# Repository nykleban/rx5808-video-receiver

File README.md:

# Smart FPV Analog RX & Spectral Analyzer

**Проєкт:** апаратно-програмний комплекс для прийому аналогового FPV-відеосигналу 5.8 GHz та сканування радіочастотного спектра в реальному часі.

---

## Про Проєкт

Цей репозиторій містить вихідний код прошивки, десктопного додатку та файли проєкту друкованої плати для розумного FPV-приймача. Система побудована на базі мікроконтролера **ATmega328P**, високочастотного модуля **RX5808** та розширеної системи керування живленням для забезпечення стабільних аналогових вимірювань.

Проєкт поєднує низькорівневе програмування вбудованих систем, розробку 4-шарової PCB з високими вимогами до розведення RF, силових та аналогових вузлів, а також десктопний аналізатор на Python. Проєкт розроблено в рамках інженерно-практичної роботи програми робототехніки Інституту ІТ та бізнесу.

Плата спроєктована в KiCad і замовлена через JLCPCB. На момент підготовки репозиторію плата ще не доставлена, тому в репозиторії подані проєктні матеріали: схема, PCB-layout, production-файли, 3D-рендери та скріншоти програмної частини.

---

## Основні Характеристики системи

### Hardware

- **RF-модуль:** приймач **RX5808 5.8 GHz** із керуванням через SPI для вибору частоти.
- **Мікроконтролер:** **ATmega328P** із зовнішнім кварцовим резонатором 16 MHz.
- **Power Management:** контролер заряду **Texas Instruments BQ25703A**, апаратний захист акумулятора **HY2120-CB**, шунти для вимірювання струму.
- **Інтерфейси:** **USB Type-C**, **CP2102N USB-to-UART**, торцевий **SMA edge-mount** роз'єм для FPV-антени.

### Software

- **Firmware C/C++:** прошивка для ATmega328P із керуванням RX5808 через SPI, зчитуванням RSSI через ADC, I2C-взаємодією з BQ25703A та serial logging.
- **Python GUI:** десктопний додаток для візуалізації RSSI в реальному часі та перевірки рівня сигналу на обраній частоті.

---

## Основні можливості

- прийом аналогового FPV-сигналу 5.8 GHz через RX5808;
- перемикання FPV-частот через SPI-керування RX5808;
- зчитування RSSI для оцінки рівня сигналу;
- виведення band, channel, frequency та RSSI через serial log;
- візуалізація RSSI в desktop analyzer у реальному часі;
- підготовлена 4-шарова PCB з окремими RF, MCU та power-management блоками;
- production package для виготовлення плати.

---

## Архітектура Друкованої Плати (PCB Layout)

Плата розроблена як 4-шарова PCB товщиною 1.6 мм з урахуванням суворих правил трасування:

1. **Ізоляція шумів:** силовий імпульсний блок з BQ25703A максимально віддалений від аналогової частини приймача RX5808.
2. **Розділення функціональних блоків:** RF, MCU, USB/UART та power-management частини винесені в окремі зони плати.
3. **Екранування:** GND-полігони використовуються для зменшення шумів і покращення стабільності аналогових вимірювань.
4. **Production-ready структура:** підготовлено BOM, positions, designators, IPC netlist і production archive для виготовлення плати.

---

## Firmware

Прошивка для ATmega328P реалізує:

- SPI-керування RX5808;
- вибір FPV-частоти;
- зчитування RSSI через ADC;
- I2C-взаємодію з power-management контролером;
- serial logging для перевірки каналу, частоти та RSSI.

Файл прошивки: `CODE/fpv_receiver.ino`

---

## Desktop analyzer

Python-додаток використовується для перегляду RSSI в реальному часі. Він дає змогу візуально порівнювати рівень сигналу на різних каналах і бачити стабільність прийому.

Використані технології: Python, PyQt5, pyqtgraph, pyserial, NumPy.

Файл додатку: `CODE/main.py`

---

## Структура репозиторію

```text
.
├── CODE/                         # firmware and desktop analyzer
│   ├── fpv_receiver.ino
│   └── main.py
├── IMAGES/                       # renders, schematics and analyzer screenshots
├── Custom_Libs/                  # custom KiCad symbols and footprints
├── production/                   # BOM, positions, designators, netlist
├── atmega328.kicad_pcb           # PCB layout
├── atmega328.kicad_sch           # main schematic
├── mcu_atmega_spi.kicad_sch      # MCU/SPI schematic block
├── rx5808_rf.kicad_sch           # RF schematic block
├── power_usb_battery_buck.kicad_sch
└── production.zip
```

---

## Візуальні матеріали

### PCB та схема

### RSSI analyzer

---

## Production files

Папка `production/` містить матеріали для виготовлення та перевірки плати:

- `bom.csv`;
- `positions.csv`;
- `designators.csv`;
- `netlist.ipc`;
- `atmega328.zip`.

Також у корені є `production.zip` як готовий архів production package.

---

## Поточний статус

- schematic design completed;
- 4-layer PCB layout completed;
- production files generated;
- PCB ordered through JLCPCB;
- firmware and desktop analyzer added to the repository;
- RSSI analyzer screenshots included.

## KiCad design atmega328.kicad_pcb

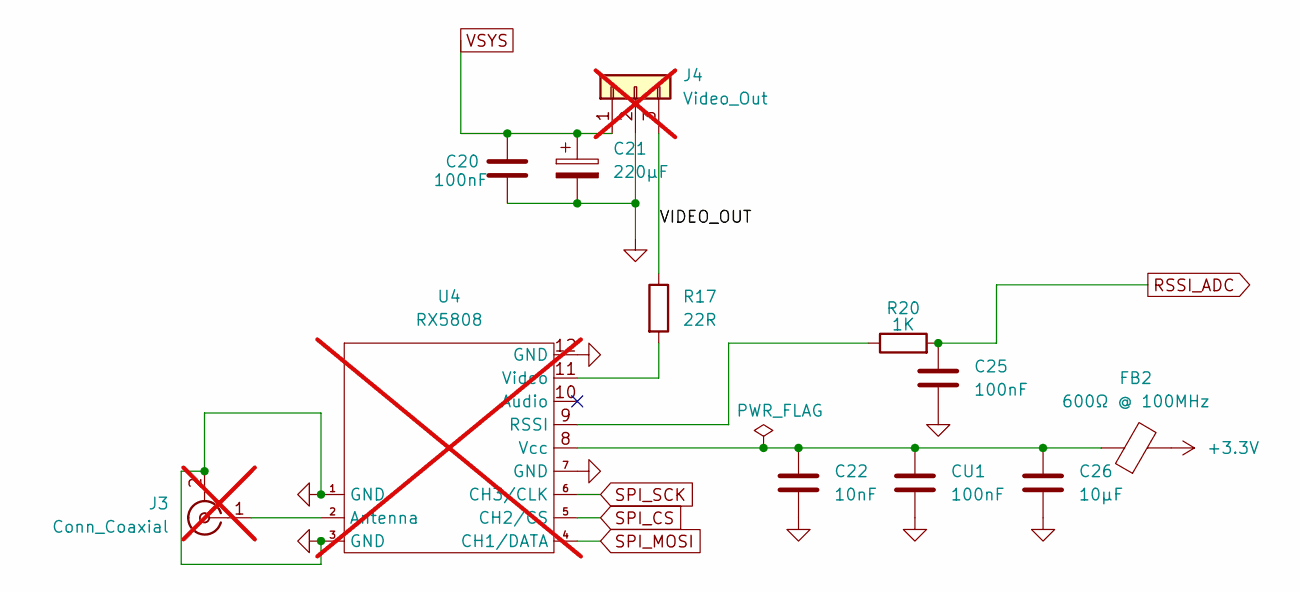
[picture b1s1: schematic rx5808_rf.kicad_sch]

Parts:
C20, C25: 100nF; C_0805_2012Metric; LCSC C1711
C21: 220µF; CP_Elec_8x10; LCSC C136294
C22: 10nF; C_0805_2012Metric; LCSC C1710
C26: 10µF; C_0805_2012Metric; LCSC C7469956
CU1: 100nF; C_0805_2012Metric; LCSC C1711
FB2: 600Ω @ 100MHz; R_0805_2012Metric; LCSC C21519
J3: Conn_Coaxial; SMA_Amphenol_132289_EdgeMount; LCSC C20415780; not fitted
J4: Video_Out; PinHeader_1x03_P2.54mm_Vertical; not fitted
R17: 22R; R_0805_2012Metric; LCSC C441970
R20: 1К; R_0805_2012Metric; LCSC C844939
U4: RX5808; not fitted

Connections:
+3.3V: FB2.2; also elsewhere on the board
/RX5808/VIDEO_OUT: J4.3, R17.1
GND: C20.2, C21.2, C22.2, C25.2, C26.2, CU1.2, J3.2 (Ext), J4.2, U4.1 (GND), U4.3 (GND), U4.7 (GND), U4.12 (GND); also elsewhere on the board
unnamed: J3.1 (In), U4.2 (Antenna)
unnamed: R20.1, U4.9 (RSSI)
unnamed: C22.1, C26.1, CU1.1, FB2.1, U4.8 (Vcc)
unnamed: R17.2, U4.11 (Video)
RSSI_ADC: C25.1, R20.2; also elsewhere on the board
SPI_CS: U4.5 (CH2/CS); also elsewhere on the board
SPI_MOSI: U4.4 (CH1/DATA); also elsewhere on the board
SPI_SCK: U4.6 (CH3/CLK); also elsewhere on the board
VSYS: C20.1, C21.1, J4.1; also elsewhere on the board

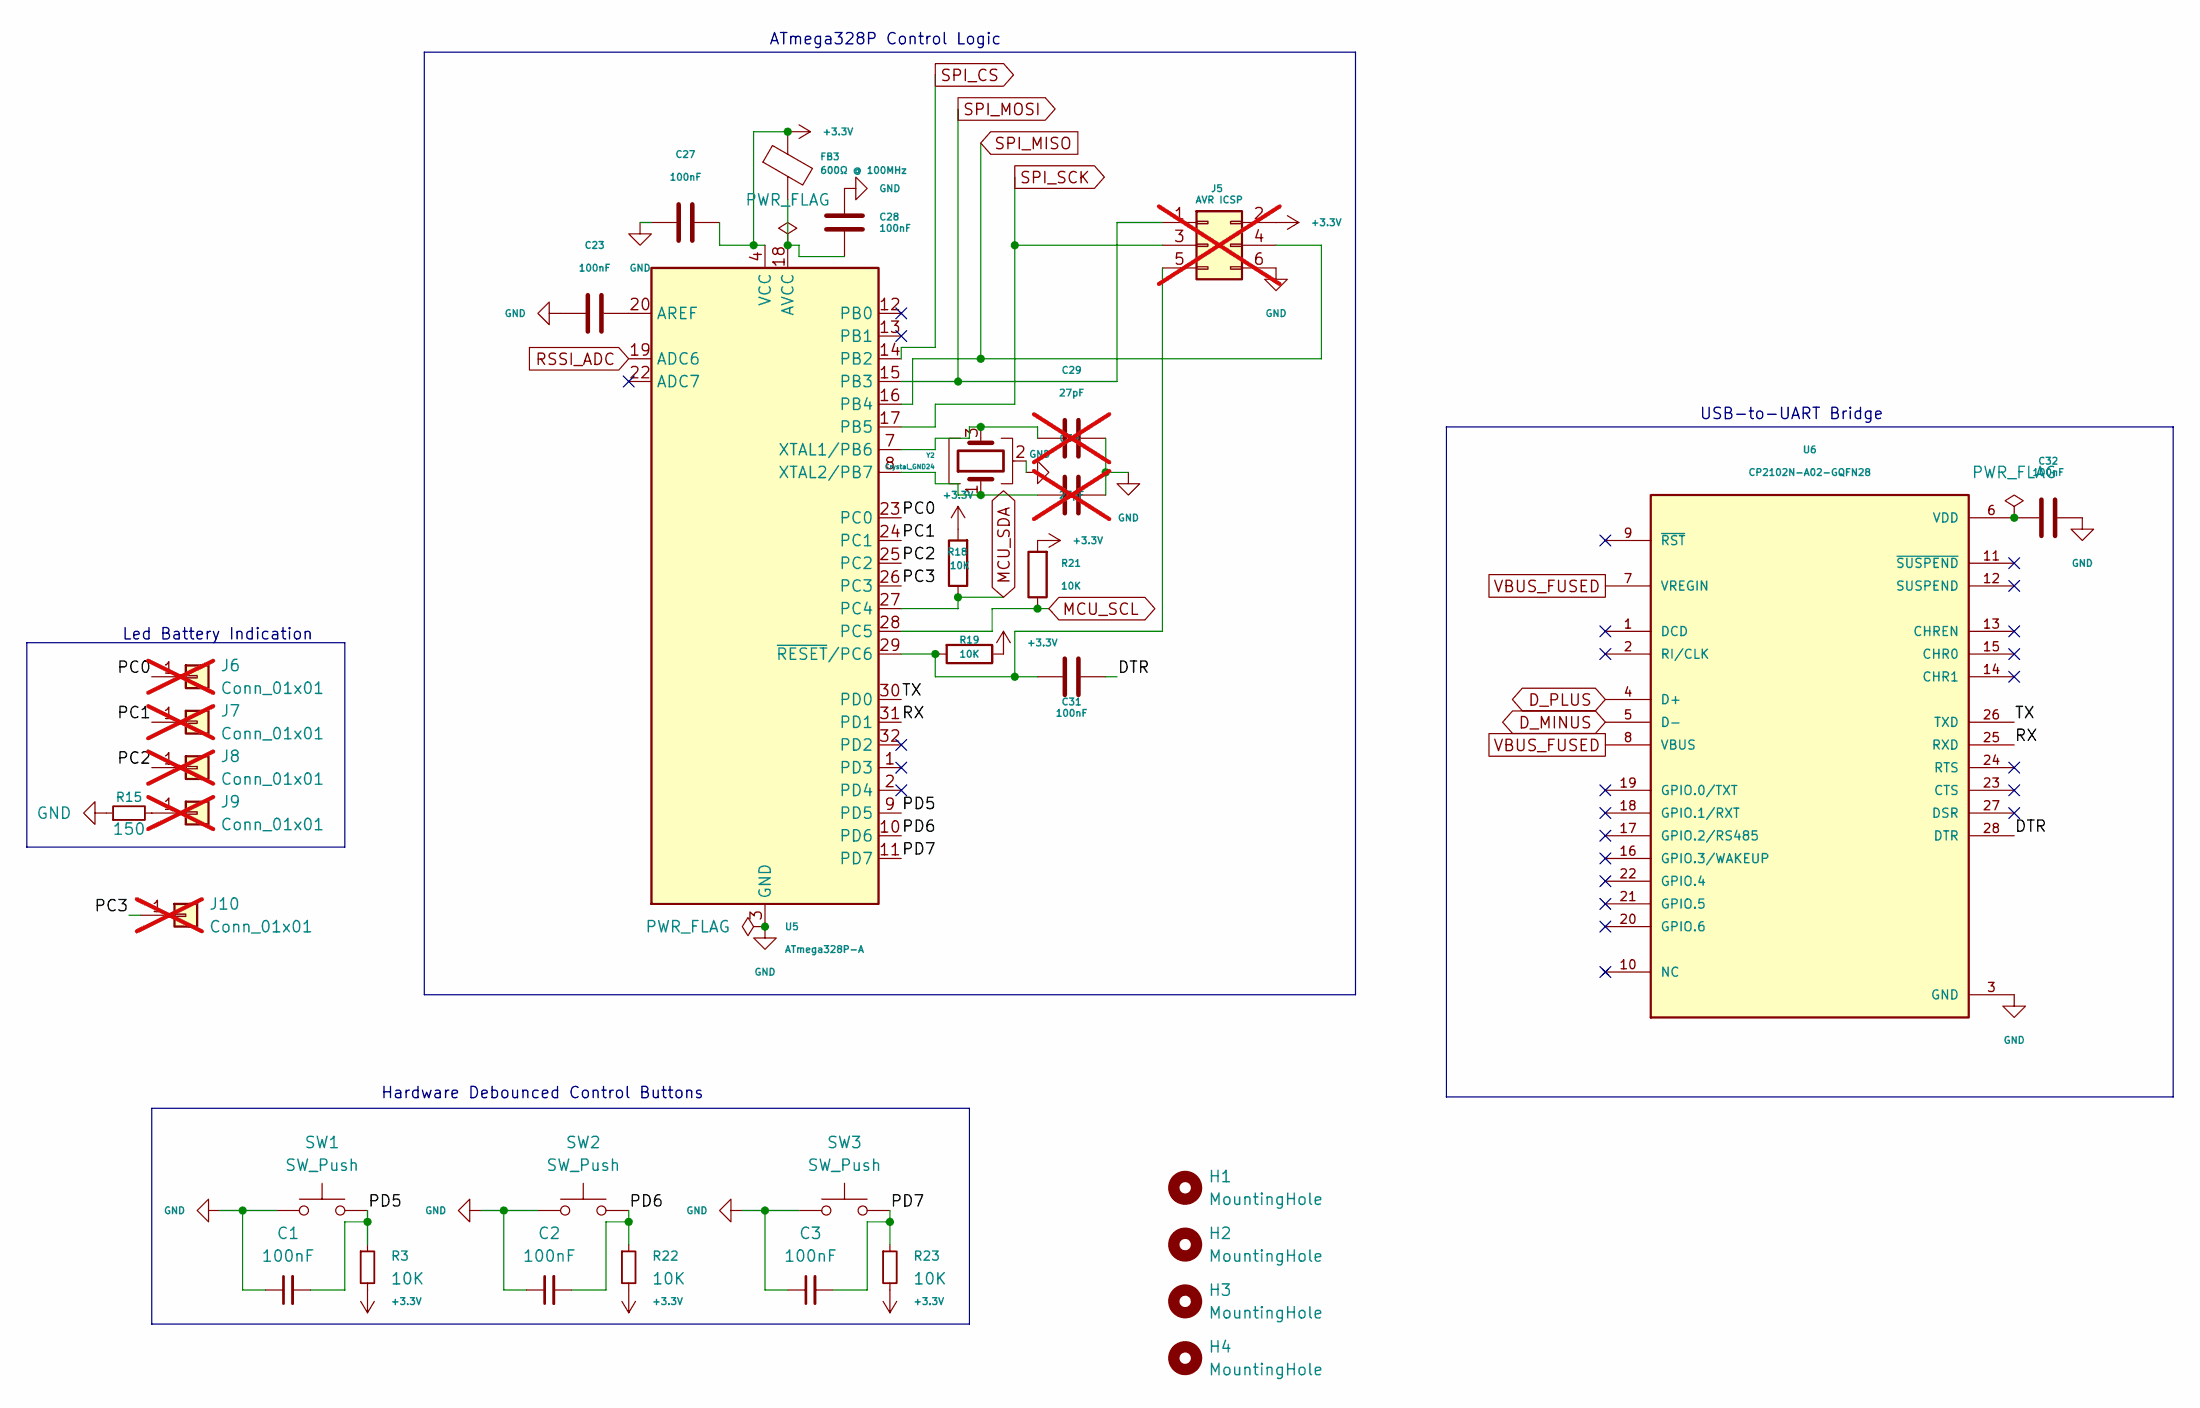
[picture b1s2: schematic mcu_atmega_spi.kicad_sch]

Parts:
C1, C2, C3, C23, C27, C28, C31, C32: 100nF; C_0805_2012Metric; LCSC C1711
C29, C30: 27pF; C_0805_2012Metric; LCSC C472840; not fitted
FB3: 600Ω @ 100MHz; R_0805_2012Metric; LCSC C21519
H1, H2, H3, H4: MountingHole; MountingHole_3.2mm_M3
J5: AVR ICSP; PinHeader_2x03_P2.54mm_Vertical; not fitted
J6, J7, J8, J9, J10: Conn_01x01; PinHeader_1x01_P2.54mm_Vertical; not fitted
R3, R18, R19, R21, R22, R23: 10K; R_0805_2012Metric; LCSC C543567
R15: 150; R_0805_2012Metric; LCSC C2933324
SW1, SW2, SW3: SW_Push; SW_SPST_PTS645Sx43SMTR92; LCSC C2834918
U5: ATmega328P-A; TQFP-32_7x7mm_P0.8mm; LCSC C14877
U6: CP2102N-A02-GQFN28; QFN-28-1EP_5x5mm_P0.5mm_EP3.1x3.1mm_ThermalVias; PARTREV 1.5; LCSC C964632
Y2: Crystal_GND24; Crystal_SMD_3225-4Pin_3.2x2.5mm; LCSC C7275095

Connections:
+3.3V: C27.2, FB3.1, J5.2, R3.2, R18.2, R19.1, R21.2, R22.2, R23.2, U5.4 (VCC), U5.6 (VCC); also elsewhere on the board
/MCU_Block/DTR: C31.2, U6.28 (DTR)
/MCU_Block/PC0: J6.1 (Pin_1_1), U5.23 (PC0)
/MCU_Block/PC1: J7.1 (Pin_1_1), U5.24 (PC1)
/MCU_Block/PC2: J8.1 (Pin_1_1), U5.25 (PC2)
/MCU_Block/PC3: J10.1 (Pin_1_1), U5.26 (PC3)
/MCU_Block/PD5: C1.2, R3.1, SW1.2, U5.9 (PD5)
/MCU_Block/PD6: C2.2, R22.1, SW2.2, U5.10 (PD6)
/MCU_Block/PD7: C3.2, R23.1, SW3.2, U5.11 (PD7)
/MCU_Block/RX: U5.31 (PD1), U6.25 (RXD)
/MCU_Block/TX: U5.30 (PD0), U6.26 (TXD)
D_MINUS: U6.5 (D-); also elsewhere on the board
D_PLUS: U6.4 (D+); also elsewhere on the board
GND: C1.1, C2.1, C3.1, C23.1, C27.1, C28.2, C29.2, C30.2, C32.2, J5.6, R15.1, SW1.1, SW2.1, SW3.1, U5.3 (GND), U5.5 (GND), U5.21 (GND), U6.3 (GND), U6.29 (GND), Y2.2 (G), Y2.4 (G); also elsewhere on the board
MCU_SCL: R21.1, U5.28 (PC5); also elsewhere on the board
MCU_SDA: R18.1, U5.27 (PC4); also elsewhere on the board
unnamed: C31.1, J5.5, R19.2, U5.29 (~RESET/PC6)
unnamed: J9.1 (Pin_1_1), R15.2
unnamed: C23.2, U5.20 (AREF)
unnamed: C28.1, FB3.2, U5.18 (AVCC)
unnamed: C29.1, U5.7 (XTAL1/PB6), Y2.3
unnamed: C30.1, U5.8 (XTAL2/PB7), Y2.1
unnamed: C32.1, U6.6 (VDD)
RSSI_ADC: U5.19 (ADC6); also elsewhere on the board
SPI_CS: U5.14 (PB2); also elsewhere on the board
SPI_MISO: J5.4, U5.16 (PB4)
SPI_MOSI: J5.1, U5.15 (PB3); also elsewhere on the board
SPI_SCK: J5.3, U5.17 (PB5); also elsewhere on the board
VBUS_FUSED: U6.7 (VREGIN), U6.8 (VBUS); also elsewhere on the board

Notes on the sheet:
ATmega328P Control Logic
Hardware Debounced Control Buttons
Led Battery Indication
USB-to-UART Bridge

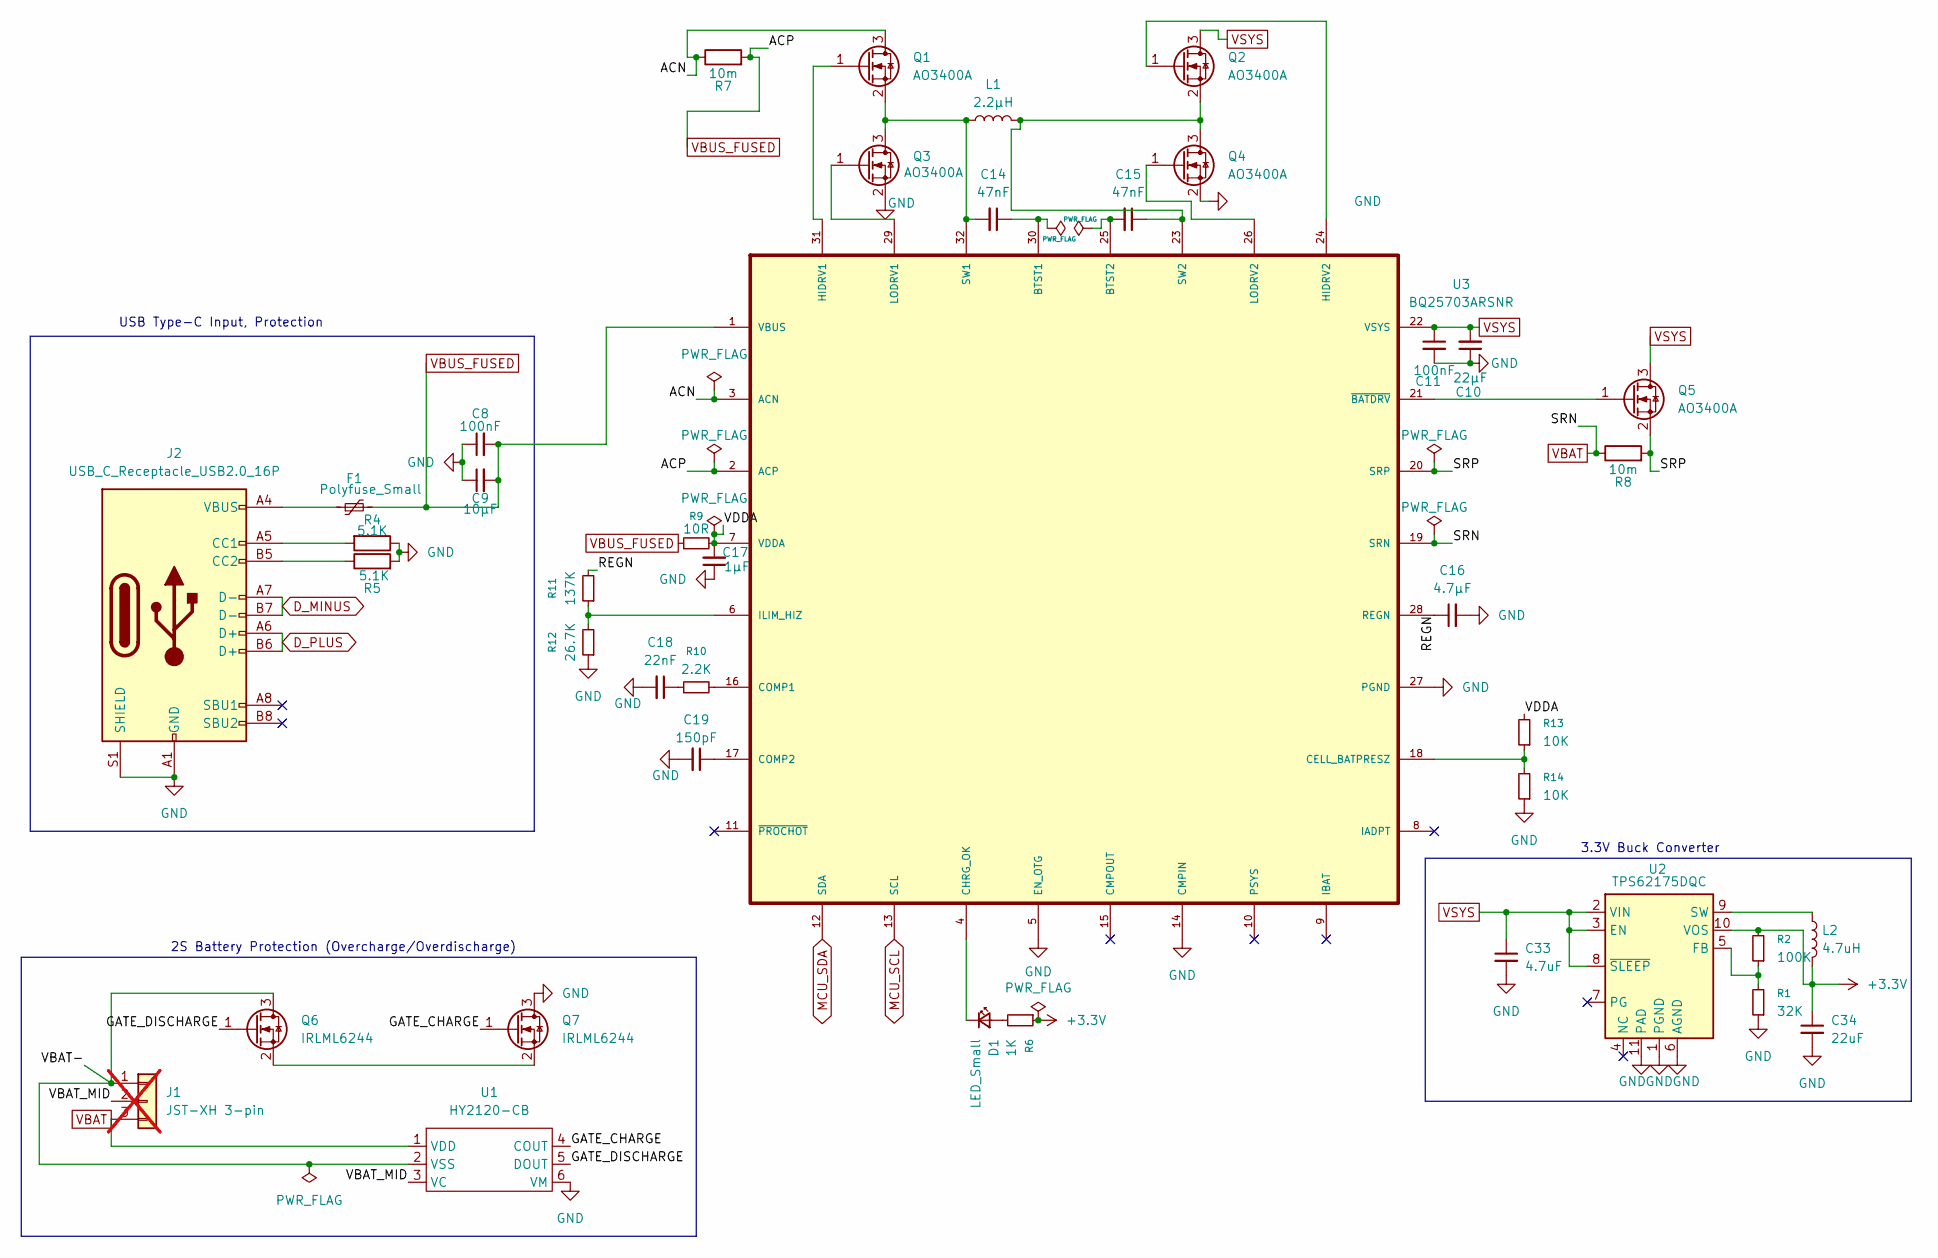
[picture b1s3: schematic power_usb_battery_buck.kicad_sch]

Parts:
C8, C11: 100nF; C_0805_2012Metric; LCSC C1711
C9: 10µF; C_0805_2012Metric; LCSC C7469956
C10: 22µF; C_0805_2012Metric; LCSC C602037
C14, C15: 47nF; C_0805_2012Metric; LCSC C53134
C16: 4.7µF; C_0805_2012Metric; LCSC C98195
C17: 1µF; C_0805_2012Metric; LCSC C1791
C18: 22nF; C_0805_2012Metric; LCSC C1729
C19: 150pF; C_0805_2012Metric; LCSC C2319426
C33: 4.7uF; C_0805_2012Metric; LCSC C98195
C34: 22uF; C_0805_2012Metric; LCSC C602037
D1: LED_Small; LED_0805_2012Metric; LCSC C84260
F1: Polyfuse_Small; Fuse_0805_2012Metric; LCSC C2840556
J1: JST-XH 3-pin; JST_XH_B3B-XH-A_1x03_P2.50mm_Vertical; not fitted
J2: USB_C_Receptacle_USB2.0_16P; USB_C_Receptacle_HRO_TYPE-C-31-M-12; LCSC C2988369
L1: 2.2µH; L_10.4x10.4_H4.8; LCSC C10164
L2: 4.7uH; L_10.4x10.4_H4.8; LCSC C19633496
Q1, Q2, Q3, Q4, Q5: AO3400A; SOT-23; LCSC C20917
Q6, Q7: IRLML6244; SOT-23; LCSC C5364311
R1: 32K; R_0805_2012Metric; LCSC C6460768
R2: 100K; R_0805_2012Metric; LCSC C441992
R4, R5: 5.1K; R_0805_2012Metric; LCSC C491151
R6: 1K; R_0805_2012Metric; LCSC C844939
R7, R8: 10m; R_1206_3216Metric; LCSC C308574
R9: 10R; R_0805_2012Metric; LCSC C844598
R10: 2.2K; R_0805_2012Metric; LCSC C441982
R11: 137K; R_0805_2012Metric; LCSC C203741
R12: 26.7K; R_0805_2012Metric; LCSC C153307
R13, R14: 10K; R_0805_2012Metric; LCSC C543567
U1: HY2120-CB; SOT-23-6_Handsoldering; LCSC C116509
U2: TPS62175DQC; WSON-10-1EP_2x3mm_P0.5mm_EP0.84x2.4mm_ThermalVias; LCSC C32097
U3: BQ25703ARSNR; Texas_RSN_WQFN-32-1EP_4x4mm_P0.4mm_EP2.8x2.8mm_ThermalVias; LCSC C188229

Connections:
+3.3V: C34.1, L2.2, R2.2, R6.1, U2.10 (VOS); also elsewhere on the board
/Power_Block/ACN: Q1.3 (D), R7.1, U3.3 (ACN)
/Power_Block/GATE_CHARGE: Q7.1 (G), U1.4 (COUT)
/Power_Block/GATE_DISCHARGE: Q6.1 (G), U1.5 (DOUT)
/Power_Block/REGN: C16.1, R11.2, U3.28 (REGN)
/Power_Block/SRP: Q5.2 (S), R8.2, U3.20 (SRP)
/Power_Block/VBAT-: J1.1, Q6.3 (D), U1.2 (VSS)
/Power_Block/VBAT_MID: J1.2, U1.3 (VC)
/Power_Block/VDDA: C17.2, R9.2, R13.2, U3.7 (VDDA)
D_MINUS: J2.A7 (D-), J2.B7 (D-); also elsewhere on the board
D_PLUS: J2.A6 (D+), J2.B6 (D+); also elsewhere on the board
GND: C8.1, C9.1, C10.1, C11.2, C16.2, C17.1, C18.2, C19.2, C33.2, C34.2, J2.A1 (GND), J2.A12 (GND), J2.B1 (GND), J2.B12 (GND), J2.S1 (SHIELD), Q3.2 (S), Q4.2 (S), Q7.3 (D), R1.1, R4.1, R5.2, R12.1, R14.1, U1.6 (VM), U2.1 (PGND), U2.6 (AGND), U2.11 (PAD), U3.5 (EN_OTG), U3.14 (CMPIN), U3.27 (PGND), U3.33 (PGND); also elsewhere on the board
MCU_SCL: U3.13 (SCL); also elsewhere on the board
MCU_SDA: U3.12 (SDA); also elsewhere on the board
unnamed: C18.1, R10.1
unnamed: D1.2 (A), R6.2
unnamed: D1.1 (K), U3.4 (CHRG_OK)
unnamed: F1.1, J2.A4 (VBUS), J2.A9 (VBUS), J2.B4 (VBUS), J2.B9 (VBUS)
unnamed: J2.A5 (CC1), R4.2
unnamed: J2.B5 (CC2), R5.1
unnamed: Q1.1 (G), U3.31 (HIDRV1)
unnamed: C14.2, L1.1, Q1.2 (S), Q3.3 (D), U3.32 (SW1)
unnamed: Q2.1 (G), U3.24 (HIDRV2)
unnamed: C15.1, L1.2, Q2.2 (S), Q4.3 (D), U3.23 (SW2)
unnamed: Q3.1 (G), U3.29 (LODRV1)
unnamed: Q4.1 (G), U3.26 (LODRV2)
unnamed: Q5.1 (G), U3.21 (~BATDRV)
unnamed: Q6.2 (S), Q7.2 (S)
unnamed: R1.2, R2.1, U2.5 (FB)
unnamed: L2.1, U2.9 (SW)
unnamed: C14.1, U3.30 (BTST1)
unnamed: C15.2, U3.25 (BTST2)
unnamed: R13.1, R14.2, U3.18 (CELL_BATPRESZ)
unnamed: R10.2, U3.16 (COMP1)
unnamed: C19.1, U3.17 (COMP2)
unnamed: R11.1, R12.2, U3.6 (ILIM_HIZ)
VBAT: J1.3, R8.1, U1.1 (VDD), U3.19 (SRN)
VBUS_FUSED: C8.2, C9.2, F1.2, R7.2, R9.1, U3.1 (VBUS), U3.2 (ACP); also elsewhere on the board
VSYS: C10.2, C11.1, C33.1, Q2.3 (D), Q5.3 (D), U2.2 (VIN), U2.3 (EN), U2.8 (~SLEEP), U3.22 (VSYS); also elsewhere on the board

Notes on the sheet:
3.3V Buck Converter
USB Type-C Input, Protection
2S Battery Protection (Overcharge/Overdischarge)

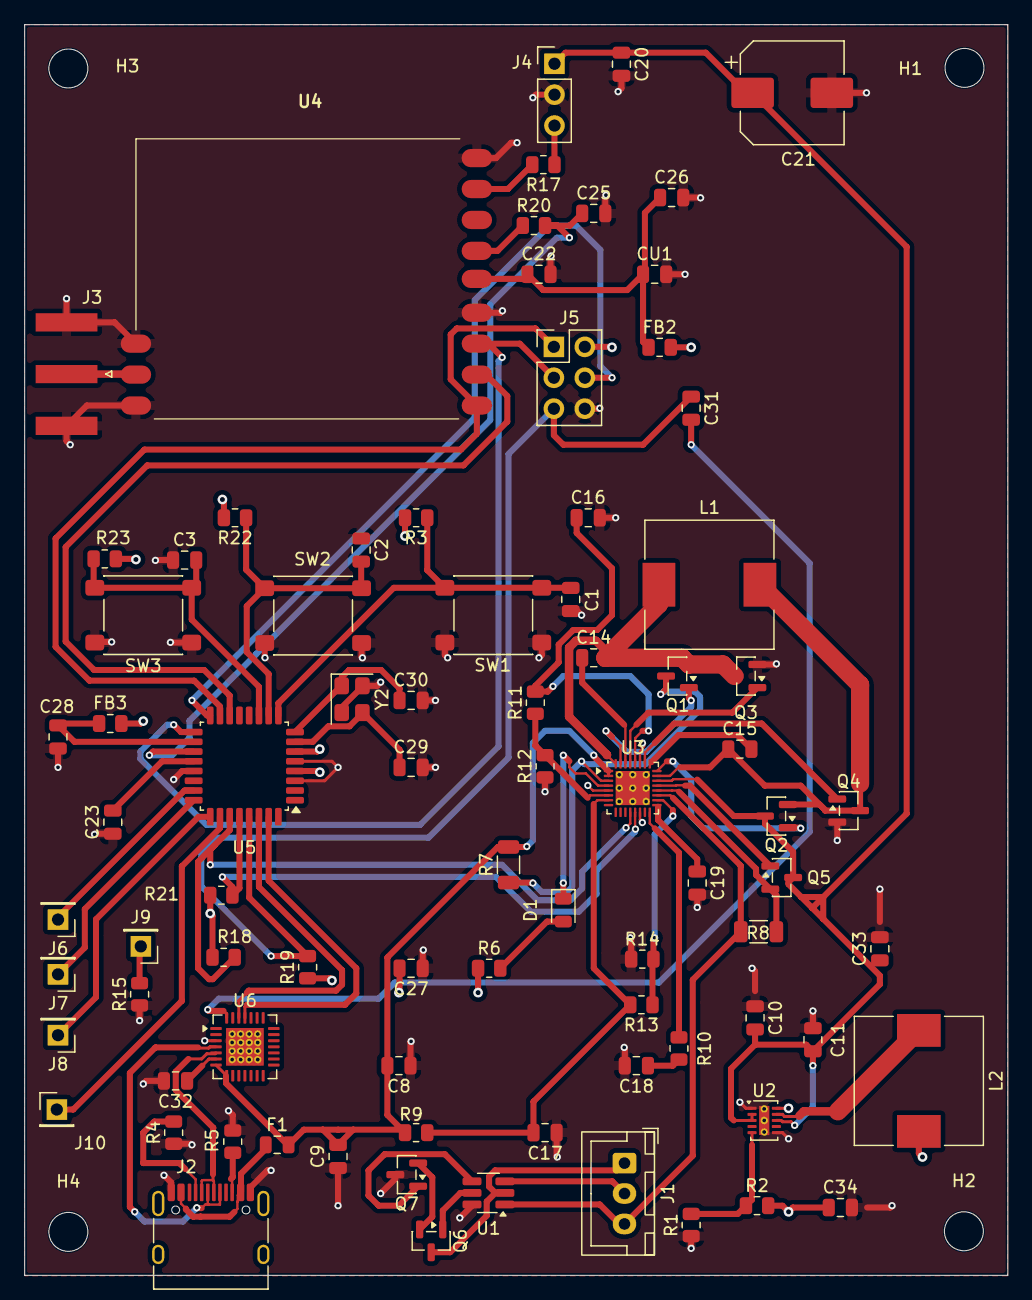
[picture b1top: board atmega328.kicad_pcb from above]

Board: 4 copper layers, 80.7 x 102.7 mm, 87 parts (0 on the bottom side), 66 nets.

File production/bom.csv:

Designator,Footprint,Quantity,Value,LCSC Part #
"C1, C11, C2, C20, C23, C25, C27, C28, C3, C31, C32, C8, CU1",0805,13,100nF,C1711
C10,0805,1,22µF,C602037
"C14, C15",0805,2,47nF,C53134
C16,0805,1,4.7µF,C98195
C17,0805,1,1µF,C1791
C18,0805,1,22nF,C1729
C19,0805,1,150pF,C2319426
C21,CP_Elec_8x10,1,220µF,C136294
C22,0805,1,10nF,C1710
"C26, C9",0805,2,10µF,C7469956
C33,0805,1,4.7uF,C98195
C34,0805,1,22uF,C602037
D1,0805,1,LED_Small,C84260
F1,0805,1,Polyfuse_Small,C2840556
"FB2, FB3",0805,2,600Ω @ 100MHz,C21519
J2,USB_C_Receptacle_HRO_TYPE-C-31-M-12,1,USB_C_Receptacle_USB2.0_16P,C2988369
L1,L_10.4x10.4_H4.8,1,2.2µH,C10164
L2,L_10.4x10.4_H4.8,1,4.7uH,C19633496
"Q1, Q2, Q3, Q4, Q5",SOT-23,5,AO3400A,C20917
"Q6, Q7",SOT-23,2,IRLML6244,C5364311
R1,0805,1,32K,C6460768
R10,0805,1,2.2K,C441982
R11,0805,1,137K,C203741
R12,0805,1,26.7K,C153307
"R13, R14, R18, R19, R21, R22, R23, R3",0805,8,10K,C543567
R15,0805,1,150,C2933324
R17,0805,1,22R,C441970
R2,0805,1,100K,C441992
R20,0805,1,1К,C844939
"R4, R5",0805,2,5.1K,C491151
R6,0805,1,1K,C844939
"R7, R8",1206,2,10m,C308574
R9,0805,1,10R,C844598
"SW1, SW2, SW3",SW_SPST_PTS645Sx43SMTR92,3,SW_Push,C2834918
U1,SOT-23-6_Handsoldering,1,HY2120-CB,C116509
U2,WSON-10-1EP_2x3mm_P0.5mm_EP0.84x2.4mm_ThermalVias,1,TPS62175DQC,C32097
U3,Texas_RSN_WQFN-32-1EP_4x4mm_P0.4mm_EP2.8x2.8mm_ThermalVias,1,BQ25703ARSNR,C188229
U5,TQFP-32_7x7mm_P0.8mm,1,ATmega328P-A,C14877
U6,QFN-28-1EP_5x5mm_P0.5mm_EP3.1x3.1mm_ThermalVias,1,CP2102N-A02-GQFN28,C964632
Y2,Crystal_SMD_3225-4Pin_3.2x2.5mm,1,Crystal_GND24,C7275095

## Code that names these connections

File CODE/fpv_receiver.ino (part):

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 *
 *  АПАРАТНЕ ПІДКЛЮЧЕННЯ (згідно схеми):
 *  ─────────────────────────────────────
 *  RX5808 CH1/DATA  → PB3 (D11) — SPI_MOSI (bit-bang)
 *  RX5808 CH2/CS    → PB2 (D10) — SPI_CS
 *  RX5808 CH3/CLK   → PB5 (D13) — SPI_SCK
 *  RX5808 RSSI      → ADC6 (A6) — Аналоговий вхід
 *
 *  SW1 (Канал ▲)    → PD5 (D5)  — INPUT_PULLUP (активний LOW)
 *  SW2 (Канал ▼)    → PD6 (D6)  — INPUT_PULLUP (активний LOW)
 *  SW3 (Автоскан)   → PD7 (D7)  — INPUT_PULLUP (активний LOW)
 *
 *  LED індикація зарядки → PC3 (через R15 150Ω) — поки не використовується МК
 *
 *  I2C (BQ25703A зарядник) → PC4/SDA, PC5/SCL
 *  BQ25703A I2C адреса: 0x6B
 *
 *  UART (CP2102N) → PD0/RX, PD1/TX — для Serial Monitor
 *
 * =============================================================
 *  ЛОГІКА КЕРУВАННЯ:
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#include <Wire.h>

// ─── ПІНИ ────────────────────────────────────────────────────
#define PIN_SPI_MOSI   11   // PB3
#define PIN_SPI_CS     10   // PB2
#define PIN_SPI_SCK    13   // PB5
#define PIN_RSSI       A6   // ADC6

#define PIN_BTN_UP      5   // PD5 — Канал ▲
#define PIN_BTN_DOWN    6   // PD6 — Канал ▼
#define PIN_BTN_SCAN    7   // PD7 — Автоскан

// ─── BQ25703A I2C ────────────────────────────────────────────
#define BQ25703A_ADDR       0x6B
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  Serial.println(F("================================="));

  // Налаштування SPI пінів (bit-bang)
  pinMode(PIN_SPI_MOSI, OUTPUT);
  pinMode(PIN_SPI_CS,   OUTPUT);
  pinMode(PIN_SPI_SCK,  OUTPUT);
  digitalWrite(PIN_SPI_CS,  HIGH);  // CS неактивний
  digitalWrite(PIN_SPI_SCK, LOW);
  digitalWrite(PIN_SPI_MOSI,LOW);

  // RSSI — аналоговий вхід (ADC6 не потребує pinMode)

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  packet |= (uint32_t)1 << 4;     // Біт 4: запис
  packet |= (uint32_t)(spiData & 0xFFFFF) << 5;  // Біти 5-24: дані (20 біт)

  digitalWrite(PIN_SPI_CS, LOW);
  delayMicroseconds(1);

  rx5808_SpiWrite(packet, 25);

  delayMicroseconds(1);
  digitalWrite(PIN_SPI_CS, HIGH);
}

/*
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 */
void rx5808_SpiWrite(uint32_t data, uint8_t bits) {
  for (uint8_t i = 0; i < bits; i++) {
    digitalWrite(PIN_SPI_MOSI, (data >> i) & 1);
    delayMicroseconds(1);
    digitalWrite(PIN_SPI_SCK, HIGH);
    delayMicroseconds(1);
    digitalWrite(PIN_SPI_SCK, LOW);
    delayMicroseconds(1);
  }
  digitalWrite(PIN_SPI_MOSI, LOW);
}

// =============================================================
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
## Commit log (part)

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2026-05-17 init
    added simple structure with minimal PCB
2026-05-18 fixed positions
2026-05-18 Revise README for Smart FPV Analog RX project
    Updated project description and features in README.
2026-05-18 fixed positions 2
2026-05-19 fixed all errors and warnings
2026-05-21 added connections
2026-05-21 fixed positions of connections
2026-05-21 added JLCPCB settings
2026-05-23 Force update local files
2026-05-24 done with lcsc
2026-05-24 done
2026-05-24 production
